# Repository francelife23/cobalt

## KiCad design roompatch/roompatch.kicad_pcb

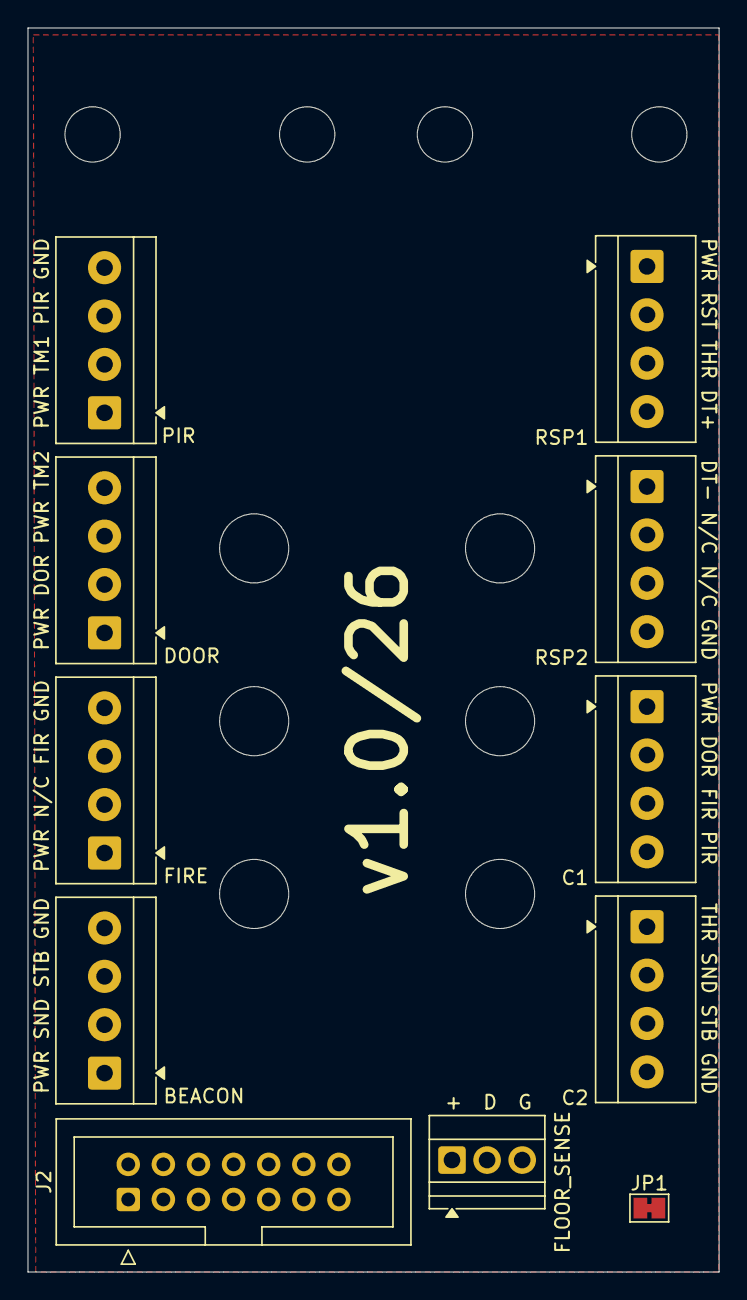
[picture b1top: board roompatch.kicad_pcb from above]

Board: 2 copper layers, 50.0 x 90.0 mm, 27 parts (0 on the bottom side), 16 nets, no tracks yet.

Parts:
CABLETIE1, CABLETIE2, CABLETIE3, CABLETIE4, CABLETIE5, CABLETIE6, CABLETIE7, CABLETIE8, CABLETIE9, CABLETIE10: MountingHole_4mm
DINMNTA1, DINMNTA2, DINMNTA3: MountingHole_5mm
DINMNTB1, DINMNTB2, DINMNTB3: MountingHole_5mm
IDC1: PIR; TerminalBlock_4Ucon_1x04_P3.50mm_Horizontal
IDC2: DOOR; TerminalBlock_4Ucon_1x04_P3.50mm_Horizontal
IDC4: FIRE; TerminalBlock_4Ucon_1x04_P3.50mm_Horizontal
IDC5: BEACON; TerminalBlock_4Ucon_1x04_P3.50mm_Horizontal
IDC6: RSP1; TerminalBlock_4Ucon_1x04_P3.50mm_Horizontal
IDC7: RSP2; TerminalBlock_4Ucon_1x04_P3.50mm_Horizontal
IDC8: C1; TerminalBlock_4Ucon_1x04_P3.50mm_Horizontal
IDC9: C2; TerminalBlock_4Ucon_1x04_P3.50mm_Horizontal
J1: FLOOR_SENSE; TerminalBlock_Xinya_XY308-2.54-3P_1x03_P2.54mm_Horizontal
J2: ROOM CONTROLLER; IDC-Header_2x07_P2.54mm_Vertical
JP1: THERMO_SIG; SolderJumper-2_P1.3mm_Bridged_Pad1.0x1.5mm

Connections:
+5V: J1.1, J2.1
+POWER: IDC1.1, IDC2.1, IDC2.3, IDC4.1, IDC5.1, IDC6.1, IDC8.1, J2.14
FLOOR_TEMP_DATA: J1.2, J2.5
GND: IDC1.4, IDC4.4, IDC5.4, IDC7.4, IDC9.4, J1.3, J2.6
INPUT_DOOR: IDC2.2, IDC8.2, J2.2
INPUT_FIRE: IDC4.3, IDC8.3, J2.13
INPUT_PIR: IDC1.3, IDC8.4, J2.12
INPUT_TAMP1: IDC1.2, J2.3
INPUT_TAMP2: IDC2.4, J2.4
RSP_DATA+: IDC6.4, J2.8
RSP_DATA-: IDC7.1, J2.7
RSP_RST: IDC6.2, J2.9
SOUNDER: IDC5.2, IDC9.2, J2.11
STROBE: IDC5.3, IDC9.3, J2.10
THERMOSTAT_SIG_IN: IDC6.3, JP1.2 (B)
THERMOSTAT_SIG_OUT: IDC9.1, JP1.1 (A)

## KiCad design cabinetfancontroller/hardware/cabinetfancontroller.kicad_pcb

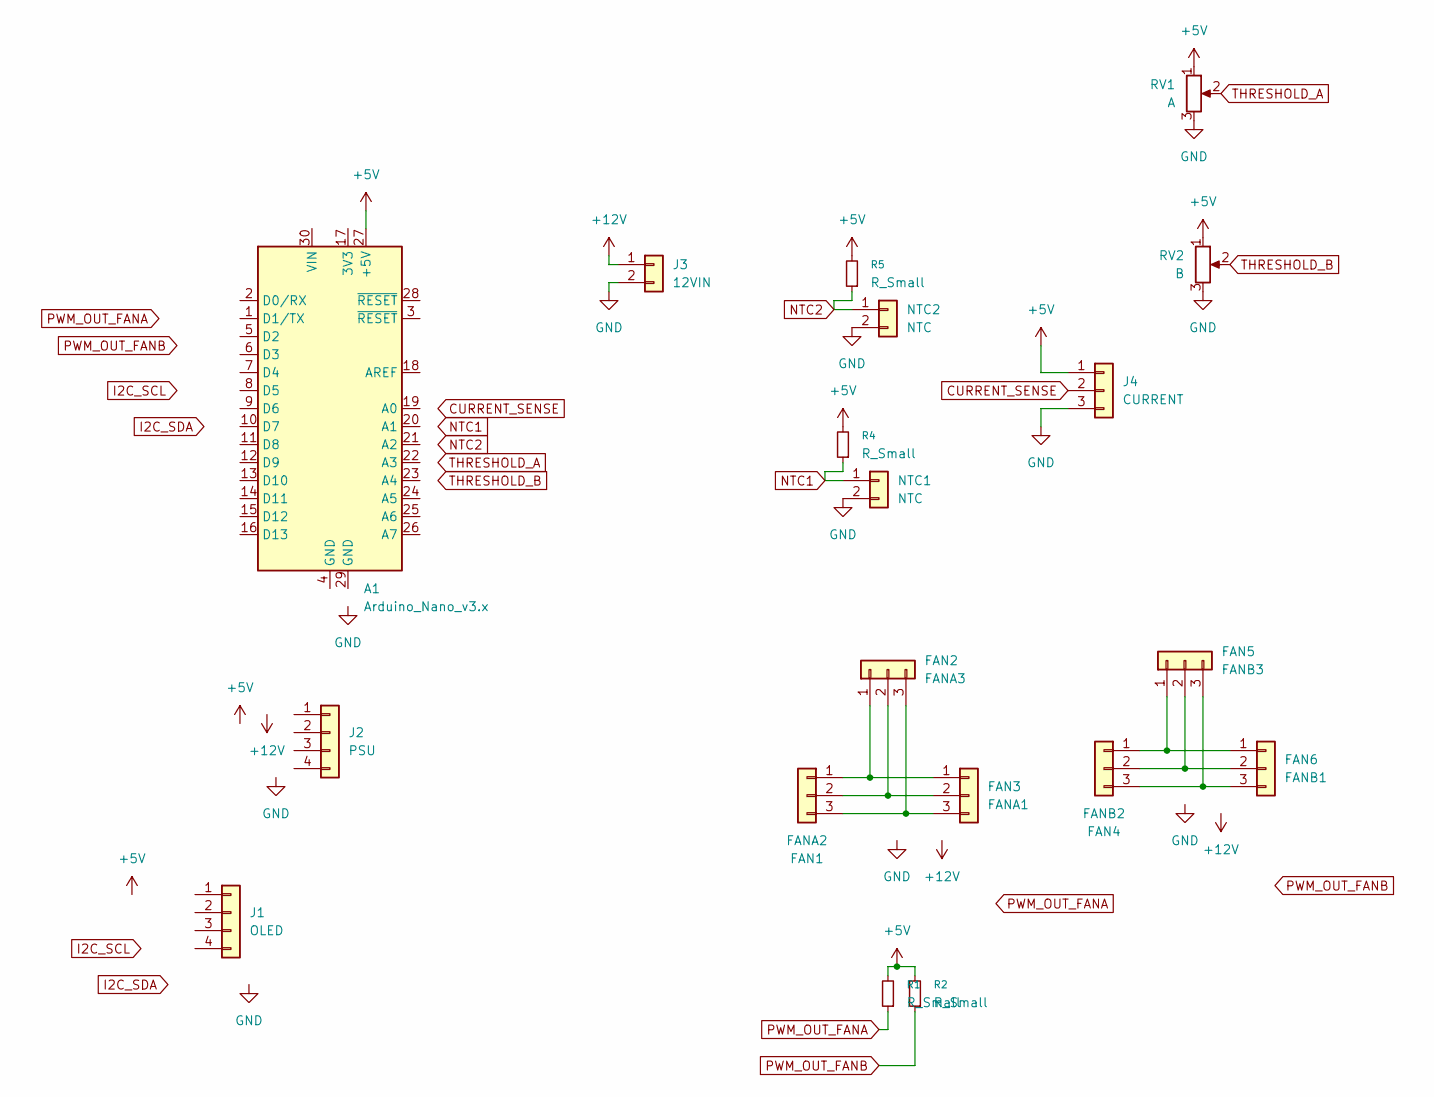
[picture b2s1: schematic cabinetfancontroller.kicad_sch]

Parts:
A1: Arduino_Nano_v3.x; Arduino_Nano
FAN1: FANA2; PinHeader_1x03_P2.54mm_Vertical
FAN2: FANA3; PinHeader_1x03_P2.54mm_Vertical
FAN3: FANA1; PinHeader_1x03_P2.54mm_Vertical
FAN4: FANB2; PinHeader_1x03_P2.54mm_Vertical
FAN5: FANB3; PinHeader_1x03_P2.54mm_Vertical
FAN6: FANB1; PinHeader_1x03_P2.54mm_Vertical
J1: OLED; PinSocket_1x04_P2.54mm_Vertical
J2: PSU; PinHeader_1x04_P2.54mm_Vertical
J3: 12VIN; PinHeader_1x02_P2.54mm_Vertical
J4: CURRENT; PinSocket_1x03_P2.54mm_Vertical
NTC1, NTC2: NTC; PinHeader_1x02_P2.54mm_Vertical
R1, R2, R4, R5: R_Small; R_Axial_DIN0309_L9.0mm_D3.2mm_P12.70mm_Horizontal
RV1: A; Potentiometer_ACP_CA9-V10_Vertical
RV2: B; Potentiometer_ACP_CA9-V10_Vertical

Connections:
+5V: A1.27 (+5V), J4.1, R1.2, R2.2, R4.2, R5.2, RV1.1, RV2.1
+12V: J3.1
CURRENT_SENSE: J4.2
GND: J3.2, J4.3, NTC1.2, NTC2.2, RV1.3, RV2.3
NTC1: NTC1.1, R4.1
NTC2: NTC2.1, R5.1
unnamed: FAN1.1, FAN2.1, FAN3.1
unnamed: FAN1.2, FAN2.2, FAN3.2
unnamed: FAN1.3, FAN2.3, FAN3.3
unnamed: FAN4.1, FAN5.1, FAN6.1
unnamed: FAN4.2, FAN5.2, FAN6.2
unnamed: FAN4.3, FAN5.3, FAN6.3
PWM_OUT_FANA: R1.1
PWM_OUT_FANB: R2.1
THRESHOLD_A: RV1.2
THRESHOLD_B: RV2.2

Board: 2 copper layers, 19 parts (0 on the bottom side), 10 nets, no tracks yet.

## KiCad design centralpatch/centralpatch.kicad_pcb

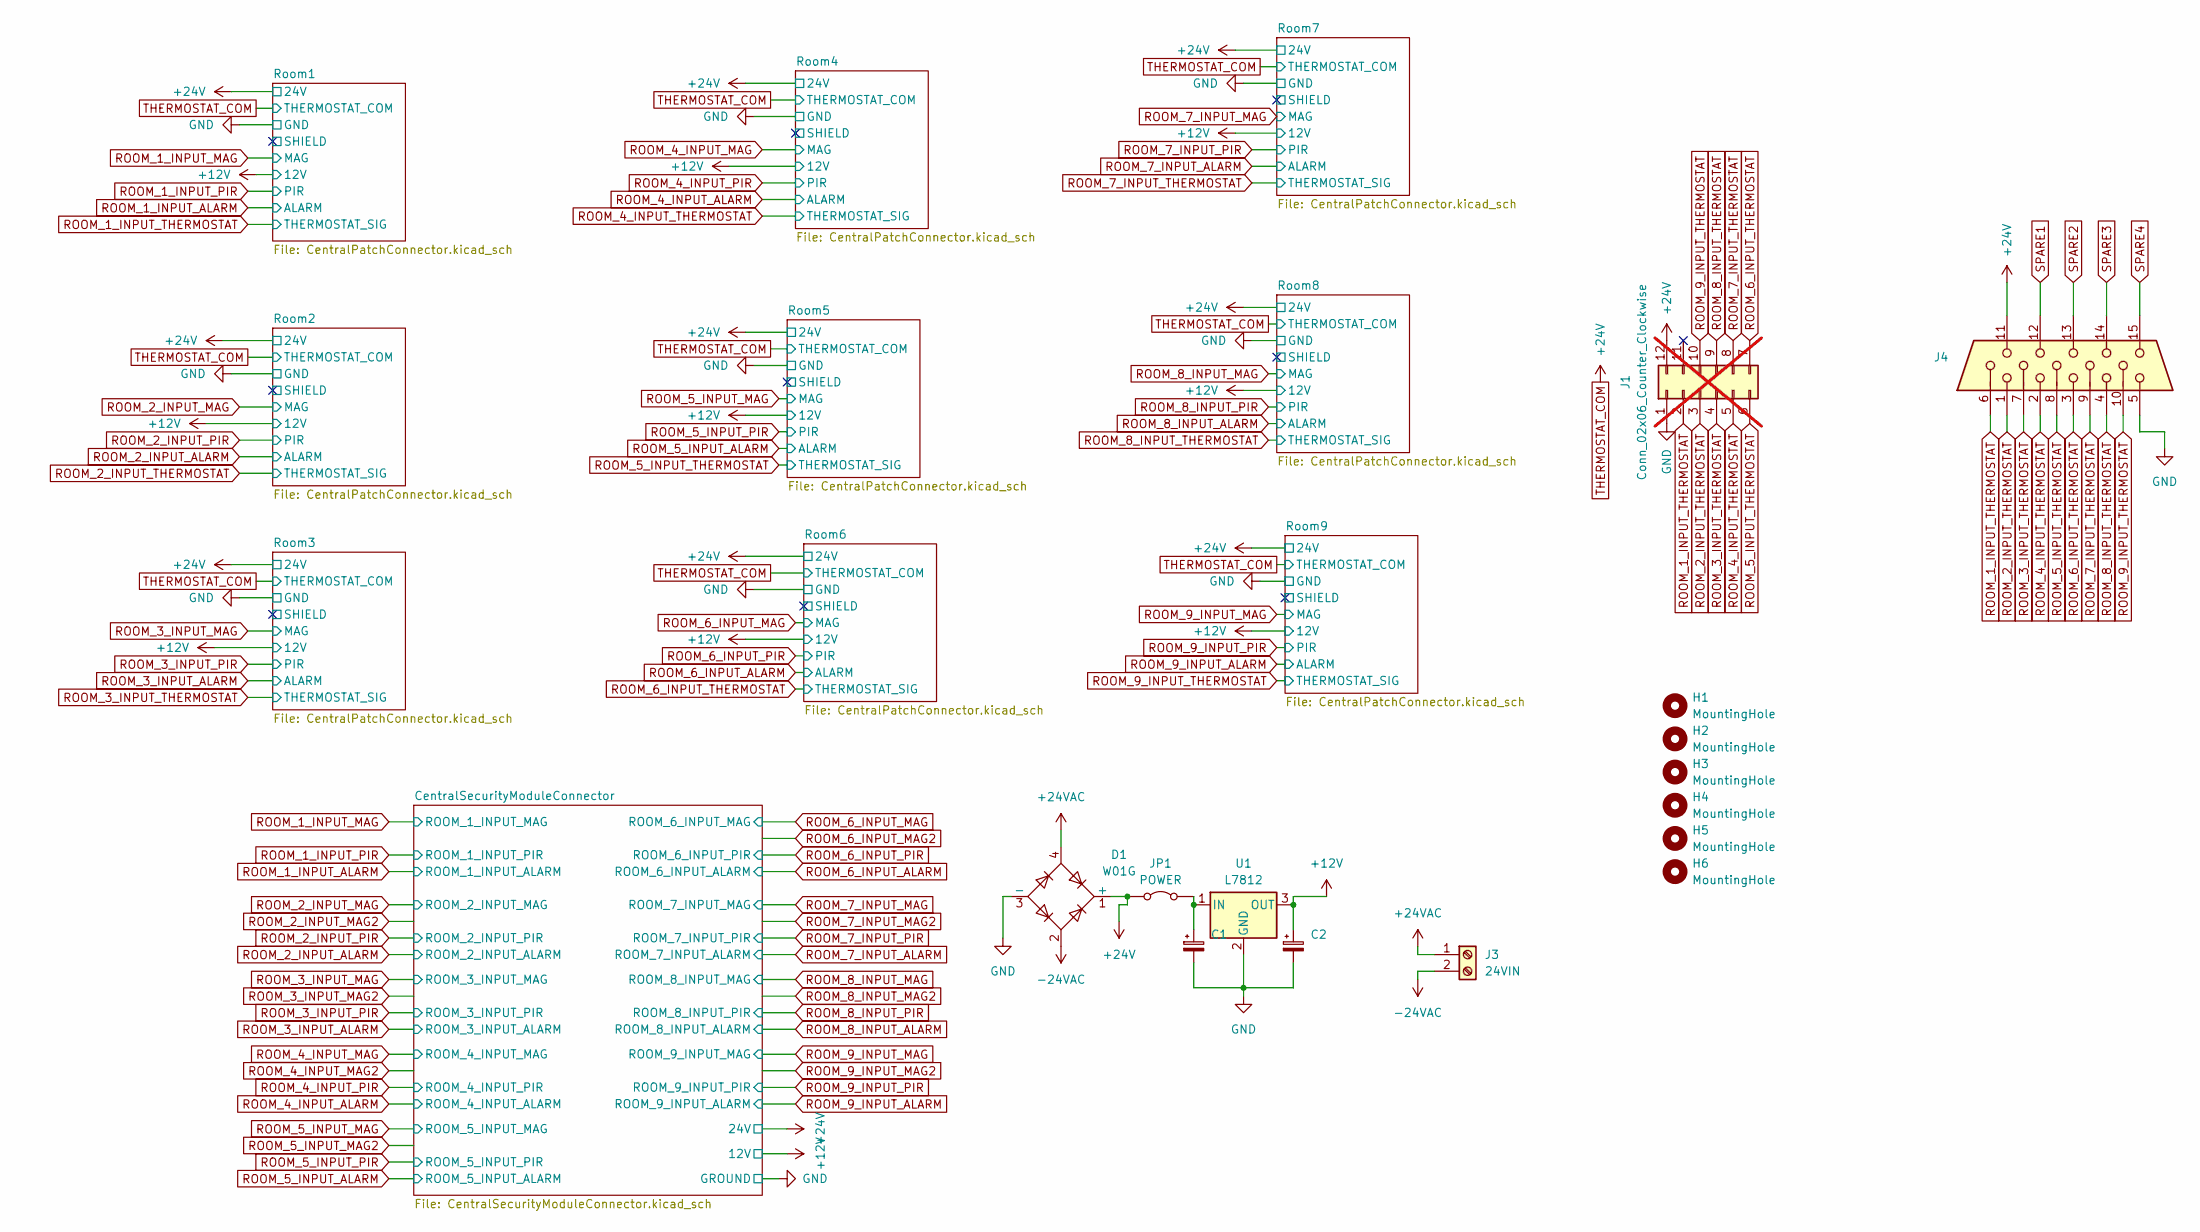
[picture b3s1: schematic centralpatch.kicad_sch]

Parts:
C1, C2: C_Polarized_Small; CP_Radial_D8.0mm_P2.50mm
D1: W01G; Diode_Bridge_Round_D9.8mm
H1, H2, H3, H4, H5, H6: MountingHole; MountingHole_2.2mm_M2
J1: Conn_02x06_Counter_Clockwise; IDC-Header_2x06_P2.54mm_Horizontal; not fitted
J3: 24VIN; TerminalBlock_MaiXu_MX126-5.0-02P_1x02_P5.00mm
J4: DE15_Socket_HighDensity; DSUB-15_Socket_Vertical_P2.77x2.84mm
JP1: POWER; SolderJumper-2_P1.3mm_Bridged_Pad1.0x1.5mm
U1: L7812; TO-3P-3_Horizontal_TabUp

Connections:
+12V: C2.1, U1.3 (OUT); also elsewhere on the board
+24VAC: D1.4, J3.1
-24VAC: D1.2, J3.2
GND: C1.2, C2.2, D1.3 (-), J1.1, J4.5, U1.2 (GND); also elsewhere on the board
unnamed: C1.1, JP1.2 (B), U1.1 (IN)
ROOM_1_INPUT_THERMOSTAT: J1.2, J4.6; also elsewhere on the board
ROOM_2_INPUT_THERMOSTAT: J1.3, J4.1; also elsewhere on the board
ROOM_3_INPUT_THERMOSTAT: J1.4, J4.7; also elsewhere on the board
ROOM_4_INPUT_THERMOSTAT: J1.5, J4.2; also elsewhere on the board
ROOM_5_INPUT_THERMOSTAT: J1.6, J4.8; also elsewhere on the board
ROOM_6_INPUT_THERMOSTAT: J1.7, J4.3; also elsewhere on the board
ROOM_7_INPUT_THERMOSTAT: J1.8, J4.9; also elsewhere on the board
ROOM_8_INPUT_THERMOSTAT: J1.9, J4.4; also elsewhere on the board
ROOM_9_INPUT_THERMOSTAT: J1.10, J4.10; also elsewhere on the board
SPARE1: J4.12
SPARE2: J4.13
SPARE3: J4.14
SPARE4: J4.15
THERMOSTAT_COM: D1.1 (+), J1.12, J4.11, JP1.1 (A); also elsewhere on the board

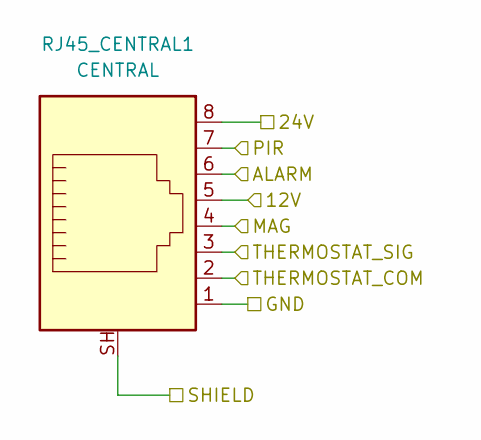
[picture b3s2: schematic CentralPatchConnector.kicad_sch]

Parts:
RJ45_CENTRAL1: CENTRAL; RJ45_HALO_HFJ11-x2450HRL_Horizontal

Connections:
+12V: RJ45_CENTRAL1.5; also elsewhere on the board
/Room1/SHIELD: RJ45_CENTRAL1.SH
/Room1/SHIELD_1: RJ45_CENTRAL1.SH
GND: RJ45_CENTRAL1.1; also elsewhere on the board
ROOM_1_INPUT_ALARM: RJ45_CENTRAL1.6; also elsewhere on the board
ROOM_1_INPUT_MAG: RJ45_CENTRAL1.4; also elsewhere on the board
ROOM_1_INPUT_PIR: RJ45_CENTRAL1.7; also elsewhere on the board
ROOM_1_INPUT_THERMOSTAT: RJ45_CENTRAL1.3; also elsewhere on the board
THERMOSTAT_COM: RJ45_CENTRAL1.2, RJ45_CENTRAL1.8; also elsewhere on the board

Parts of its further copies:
RJ45_CENTRAL2, RJ45_CENTRAL3, RJ45_CENTRAL4, RJ45_CENTRAL5, RJ45_CENTRAL6, RJ45_CENTRAL7, RJ45_CENTRAL8, RJ45_CENTRAL9: CENTRAL; RJ45_HALO_HFJ11-x2450HRL_Horizontal

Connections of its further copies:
+12V: RJ45_CENTRAL2.5, RJ45_CENTRAL3.5, RJ45_CENTRAL4.5, RJ45_CENTRAL5.5, RJ45_CENTRAL6.5, RJ45_CENTRAL7.5, RJ45_CENTRAL8.5, RJ45_CENTRAL9.5; also elsewhere on the board
/Room2/SHIELD: RJ45_CENTRAL2.SH
/Room2/SHIELD_1: RJ45_CENTRAL2.SH
/Room3/SHIELD: RJ45_CENTRAL3.SH
/Room3/SHIELD_1: RJ45_CENTRAL3.SH
/Room4/SHIELD: RJ45_CENTRAL4.SH
/Room4/SHIELD_1: RJ45_CENTRAL4.SH
/Room5/SHIELD: RJ45_CENTRAL5.SH
/Room5/SHIELD_1: RJ45_CENTRAL5.SH
/Room6/SHIELD: RJ45_CENTRAL6.SH
/Room6/SHIELD_1: RJ45_CENTRAL6.SH
/Room7/SHIELD: RJ45_CENTRAL7.SH
/Room7/SHIELD_1: RJ45_CENTRAL7.SH
/Room8/SHIELD: RJ45_CENTRAL8.SH
/Room8/SHIELD_1: RJ45_CENTRAL8.SH
/Room9/SHIELD: RJ45_CENTRAL9.SH
/Room9/SHIELD_1: RJ45_CENTRAL9.SH
GND: RJ45_CENTRAL2.1, RJ45_CENTRAL3.1, RJ45_CENTRAL4.1, RJ45_CENTRAL5.1, RJ45_CENTRAL6.1, RJ45_CENTRAL7.1, RJ45_CENTRAL8.1, RJ45_CENTRAL9.1; also elsewhere on the board
ROOM_2_INPUT_ALARM: RJ45_CENTRAL2.6; also elsewhere on the board
ROOM_2_INPUT_MAG: RJ45_CENTRAL2.4; also elsewhere on the board
ROOM_2_INPUT_PIR: RJ45_CENTRAL2.7; also elsewhere on the board
ROOM_2_INPUT_THERMOSTAT: RJ45_CENTRAL2.3; also elsewhere on the board
ROOM_3_INPUT_ALARM: RJ45_CENTRAL3.6; also elsewhere on the board
ROOM_3_INPUT_MAG: RJ45_CENTRAL3.4; also elsewhere on the board
ROOM_3_INPUT_PIR: RJ45_CENTRAL3.7; also elsewhere on the board
ROOM_3_INPUT_THERMOSTAT: RJ45_CENTRAL3.3; also elsewhere on the board
ROOM_4_INPUT_ALARM: RJ45_CENTRAL4.6; also elsewhere on the board
ROOM_4_INPUT_MAG: RJ45_CENTRAL4.4; also elsewhere on the board
ROOM_4_INPUT_PIR: RJ45_CENTRAL4.7; also elsewhere on the board
ROOM_4_INPUT_THERMOSTAT: RJ45_CENTRAL4.3; also elsewhere on the board
ROOM_5_INPUT_ALARM: RJ45_CENTRAL5.6; also elsewhere on the board
ROOM_5_INPUT_MAG: RJ45_CENTRAL5.4; also elsewhere on the board
ROOM_5_INPUT_PIR: RJ45_CENTRAL5.7; also elsewhere on the board
ROOM_5_INPUT_THERMOSTAT: RJ45_CENTRAL5.3; also elsewhere on the board
ROOM_6_INPUT_ALARM: RJ45_CENTRAL6.6; also elsewhere on the board
ROOM_6_INPUT_MAG: RJ45_CENTRAL6.4; also elsewhere on the board
ROOM_6_INPUT_PIR: RJ45_CENTRAL6.7; also elsewhere on the board
ROOM_6_INPUT_THERMOSTAT: RJ45_CENTRAL6.3; also elsewhere on the board
ROOM_7_INPUT_ALARM: RJ45_CENTRAL7.6; also elsewhere on the board
ROOM_7_INPUT_MAG: RJ45_CENTRAL7.4; also elsewhere on the board
ROOM_7_INPUT_PIR: RJ45_CENTRAL7.7; also elsewhere on the board
ROOM_7_INPUT_THERMOSTAT: RJ45_CENTRAL7.3; also elsewhere on the board
ROOM_8_INPUT_ALARM: RJ45_CENTRAL8.6; also elsewhere on the board
ROOM_8_INPUT_MAG: RJ45_CENTRAL8.4; also elsewhere on the board
ROOM_8_INPUT_PIR: RJ45_CENTRAL8.7; also elsewhere on the board
ROOM_8_INPUT_THERMOSTAT: RJ45_CENTRAL8.3; also elsewhere on the board
ROOM_9_INPUT_ALARM: RJ45_CENTRAL9.6; also elsewhere on the board
ROOM_9_INPUT_MAG: RJ45_CENTRAL9.4; also elsewhere on the board
ROOM_9_INPUT_PIR: RJ45_CENTRAL9.7; also elsewhere on the board
ROOM_9_INPUT_THERMOSTAT: RJ45_CENTRAL9.3; also elsewhere on the board
THERMOSTAT_COM: RJ45_CENTRAL2.2, RJ45_CENTRAL2.8, RJ45_CENTRAL3.2, RJ45_CENTRAL3.8, RJ45_CENTRAL4.2, RJ45_CENTRAL4.8, RJ45_CENTRAL5.2, RJ45_CENTRAL5.8, RJ45_CENTRAL6.2, RJ45_CENTRAL6.8, RJ45_CENTRAL7.2, RJ45_CENTRAL7.8, RJ45_CENTRAL8.2, RJ45_CENTRAL8.8, RJ45_CENTRAL9.2, RJ45_CENTRAL9.8; also elsewhere on the board

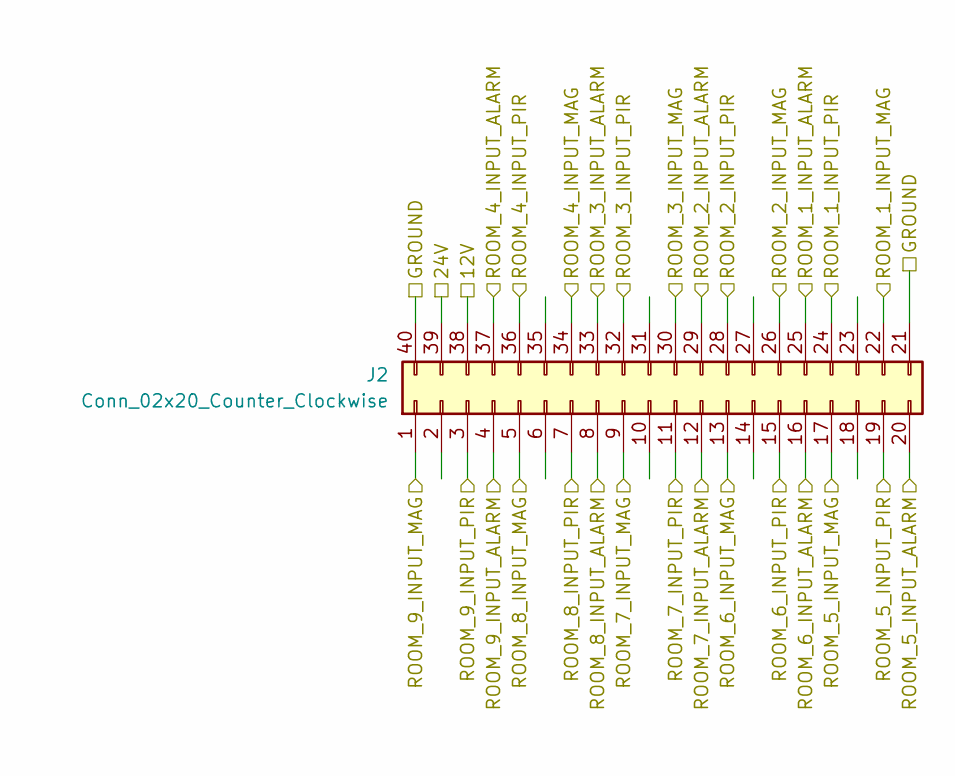
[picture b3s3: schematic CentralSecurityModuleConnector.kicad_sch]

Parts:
J2: Conn_02x20_Counter_Clockwise; IDC-Header_2x20_P2.54mm_Horizontal

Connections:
+12V: J2.38; also elsewhere on the board
GND: J2.21, J2.40; also elsewhere on the board
ROOM_1_INPUT_ALARM: J2.25; also elsewhere on the board
ROOM_1_INPUT_MAG: J2.22; also elsewhere on the board
ROOM_1_INPUT_PIR: J2.24; also elsewhere on the board
ROOM_2_INPUT_ALARM: J2.29; also elsewhere on the board
ROOM_2_INPUT_MAG: J2.26; also elsewhere on the board
ROOM_2_INPUT_PIR: J2.28; also elsewhere on the board
ROOM_3_INPUT_ALARM: J2.33; also elsewhere on the board
ROOM_3_INPUT_MAG: J2.30; also elsewhere on the board
ROOM_3_INPUT_PIR: J2.32; also elsewhere on the board
ROOM_4_INPUT_ALARM: J2.37; also elsewhere on the board
ROOM_4_INPUT_MAG: J2.34; also elsewhere on the board
ROOM_4_INPUT_PIR: J2.36; also elsewhere on the board
ROOM_5_INPUT_ALARM: J2.20; also elsewhere on the board
ROOM_5_INPUT_MAG: J2.17; also elsewhere on the board
ROOM_5_INPUT_PIR: J2.19; also elsewhere on the board
ROOM_6_INPUT_ALARM: J2.16; also elsewhere on the board
ROOM_6_INPUT_MAG: J2.13; also elsewhere on the board
ROOM_6_INPUT_PIR: J2.15; also elsewhere on the board
ROOM_7_INPUT_ALARM: J2.12; also elsewhere on the board
ROOM_7_INPUT_MAG: J2.9; also elsewhere on the board
ROOM_7_INPUT_PIR: J2.11; also elsewhere on the board
ROOM_8_INPUT_ALARM: J2.8; also elsewhere on the board
ROOM_8_INPUT_MAG: J2.5; also elsewhere on the board
ROOM_8_INPUT_PIR: J2.7; also elsewhere on the board
ROOM_9_INPUT_ALARM: J2.4; also elsewhere on the board
ROOM_9_INPUT_MAG: J2.1; also elsewhere on the board
ROOM_9_INPUT_PIR: J2.3; also elsewhere on the board
THERMOSTAT_COM: J2.39; also elsewhere on the board

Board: 2 copper layers, 23 parts (0 on the bottom side), 42 nets, no tracks yet.

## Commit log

2026-05-04 reinit
2026-06-07 20260607A
2026-06-07 20260607b
